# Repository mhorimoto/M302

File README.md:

M302 Arduino UECS SIMPLE NODE Shield 汎用簡易観測ノード
======================================================

# 概要

Arduino UNOのシールドとして UECS で農業環境計測で使用しやすい
センサ類の接続に特化した基板。

## 初版 (1.00)
  commit 2f4df36819d791f5551f218545c303c0058bd9ba
  * I2CとLANとIM920の接続インタフェースを持ったもの。

## 1.10
  * I2CとLANとADC入力とIM920の接続インタフェースを持ったもの。
  * 製作ワークショップなどで使用する用途も考慮。

## K2版 (改２

KiCAD 7.x 対応.

以下予定。

  * HX711を搭載する
  * SMDを多用する
  * W5500を搭載する
  * 電圧レベルコンバーターを搭載する

# Interface仕様

 I2Cは5V仕様。IM920を接続するためだけにレベルコンバータを使用。

## I2C

 便宜的にシルク面にJ1〜J4は名前を記しているが、いずれもI2Cなので、以下のピン配置で同じく使用できる。なお、必要に応じてセンサ側でプルアップをするように。

 | PIN | 意味 |
 |-----|------|
 |  1  | GND  |
 |  2  | +5V  |
 |  3  | SDA  |
 |  4  | SCL  |

 J5はELT社のCO2センサD-400用のインタフェースである。基本的にI2Cであるが、リセット端子を個別に用意している。

 | PIN | 意味 |
 |-----|------|
 |  1  | +5V  |
 |  2  | N/C  |
 |  3  | GND  |
 |  4  | SDA  |
 |  5  | N/C  |
 |  6  | RST  |
 |  7  | SCL  |

## アナログ入力

Arduino UNOの10bits A/Dコンバータ(以降、ADC)を手軽に使用するために4chのコネクタをJ9(ANALOG-IN)として用意している。

 | PIN | 意味 |
 |-----|------|
 |  1  | Ch1  |
 |  2  | GND  |
 |  3  | Ch2  |
 |  4  | GND  |
 |  5  | Ch3  |
 |  6  | GND  |
 |  7  | Ch4  |
 |  8  | GND  |

## IM920接続インタフェース

920MHz伝送用無線通信モジュールIM920を接続するためのシリアルインタフェースを用意している。IM920が3.3V仕様なのでレベルコンバータを実装する。(IM920を使用しない場合にはレベルコンバータは不要)

 | PIN |   意味   |
 |-----|----------|
 |  1  | RESET    |
 |  2  | BUSY     |
 |  3  | GND      |
 |  4  | +3.3V    |
 |  5  | IM920 TX |
 |  6  | IM920 RX |

## LANインタフェース

W5500で一般的に販売されているものが接続出来るように用意している。

 | PIN | 意味  |
 |-----|-------|
 |  1  | +3.3V |
 |  2  | +5V   |
 |  3  | MISO  |
 |  4  | GND   |
 |  5  | MOSI  |
 |  6  | RESET |
 |  7  | SS    |
 |  8  | N/C   |
 |  9  | SCLK  |
 | 10  | N/C   |

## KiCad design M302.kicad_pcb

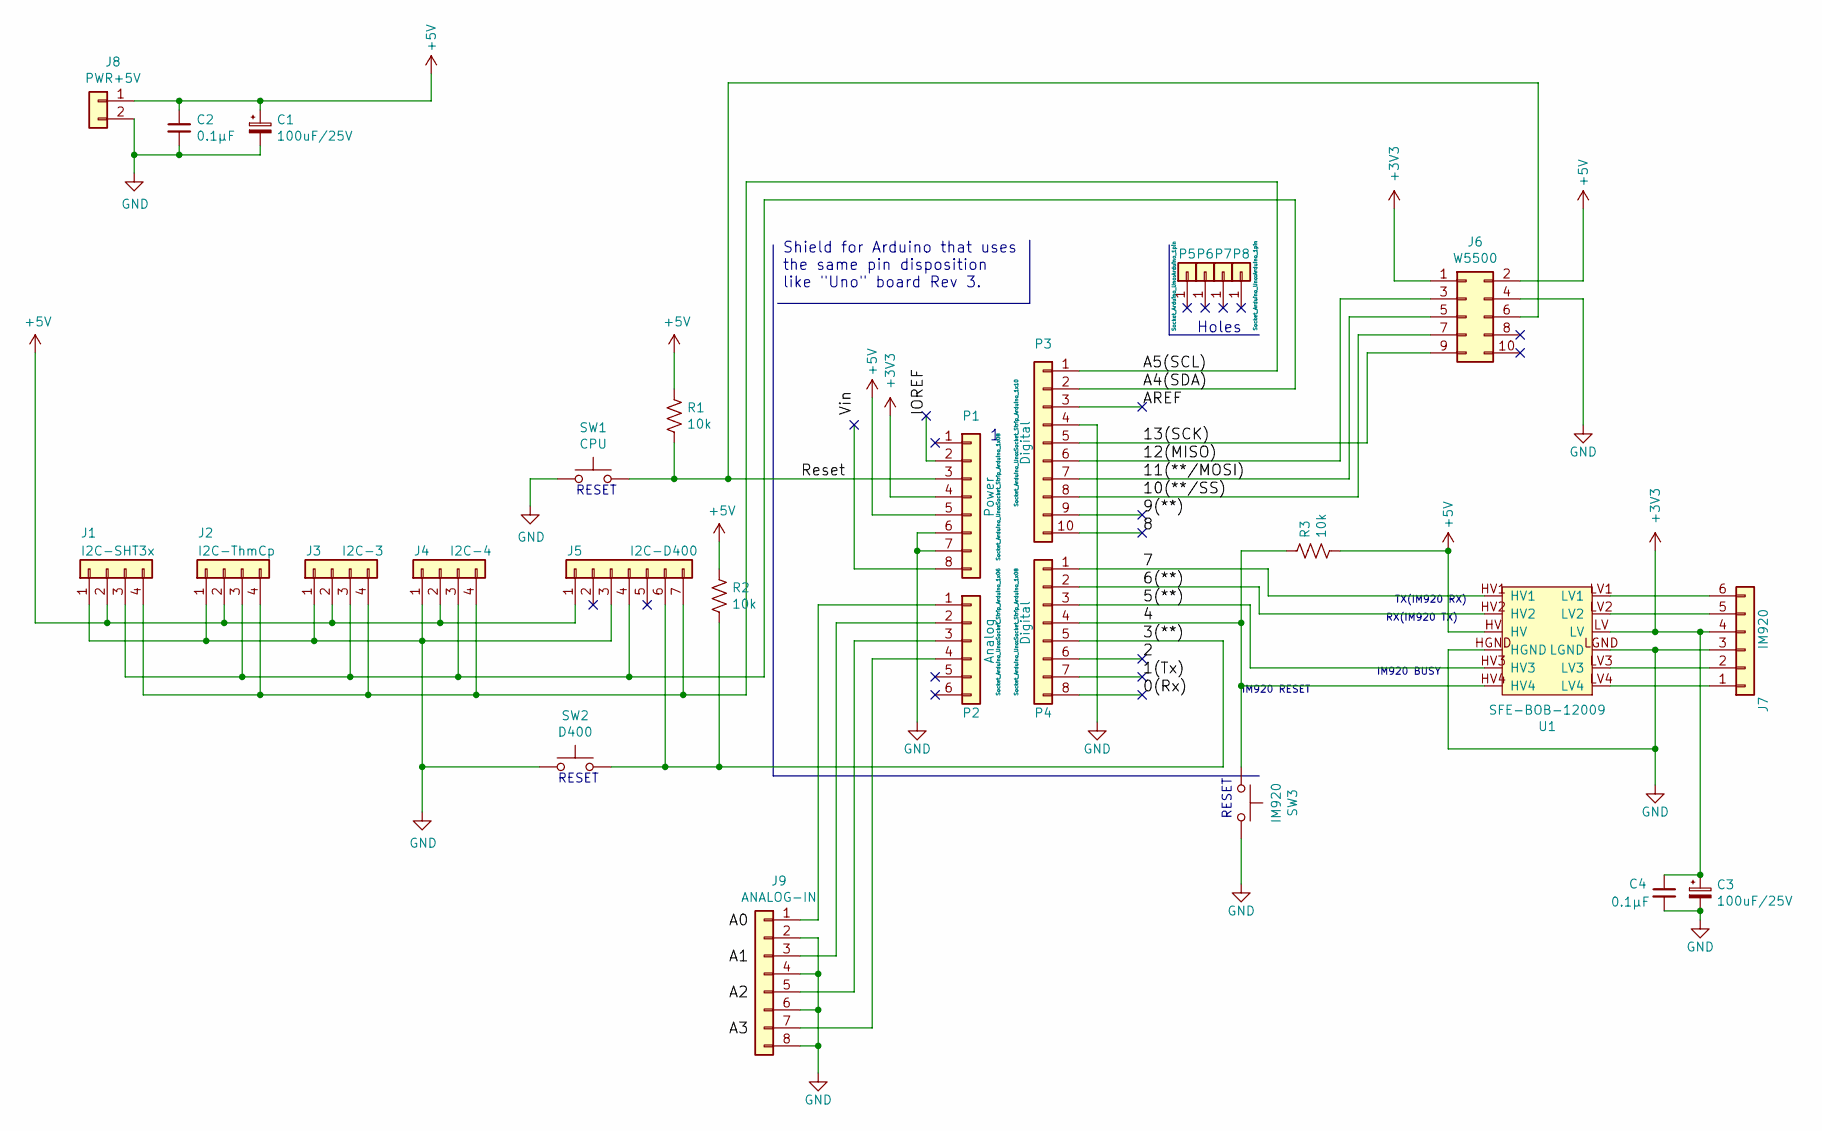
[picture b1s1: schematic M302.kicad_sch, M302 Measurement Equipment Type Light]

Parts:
C1, C3: 100uF/25V; CP_Radial_D5.0mm_P2.00mm
C2, C4: 0.1μF; C_Disc_D3.0mm_W2.0mm_P2.50mm
J1: I2C-SHT3x; JST_XH_B4B-XH-A_1x04_P2.50mm_Vertical
J2: I2C-ThmCp; JST_XH_B4B-XH-A_1x04_P2.50mm_Vertical
J3: I2C-3; JST_XH_B4B-XH-A_1x04_P2.50mm_Vertical
J4: I2C-4; JST_XH_B4B-XH-A_1x04_P2.50mm_Vertical
J5: I2C-D400; JST_XH_B7B-XH-A_1x07_P2.50mm_Vertical
J6: W5500; PinHeader_2x05_P2.54mm_Vertical
J7: IM920; JST_XH_B6B-XH-A_1x06_P2.50mm_Vertical
J8: PWR+5V; JST_XH_B2B-XH-A_1x02_P2.50mm_Vertical
J9: ANALOG-IN; JST_XH_B8B-XH-A_1x08_P2.50mm_Vertical
P1: Power; Socket_Strip_Arduino_1x08
P2: Analog; Socket_Strip_Arduino_1x06
P3: Digital; Socket_Strip_Arduino_1x10
P4: Digital; Socket_Strip_Arduino_1x08
P5, P6, P7, P8: CONN_01X01; Arduino_1pin
R1, R2, R3: 10k; R_Axial_DIN0207_L6.3mm_D2.5mm_P7.62mm_Horizontal
SW1: CPU; TVDT18-050
SW2: D400; TVDT18-050
SW3: IM920; TVDT18-050
U1: SFE-BOB-12009

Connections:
+3V3: C3.1, C4.1, J6.1, J7.4, P1.4, U1.LV
+5V: C1.1, C2.1, J1.2, J2.2, J3.2, J4.2, J5.1, J6.2, J8.1, P1.5, R1.1, R2.1, R3.2, U1.HV
/0(Rx): P4.8
/1(Tx): P4.7
/2: P4.6
/3(**): J5.6, P4.5, R2.2, SW2.2
/4: P4.4, R3.1, SW3.1, U1.HV4
/5(**): P4.3, U1.HV3
/6(**): P4.2, U1.HV2
/7: P4.1, U1.HV1
/8: P3.10
/9(**): P3.9
/10(**/SS): J6.7, P3.8
/11(**/MOSI): J6.5, P3.7
/12(MISO): J6.3, P3.6
/13(SCK): J6.9, P3.5
/A4(SDA): J1.3, J2.3, J3.3, J4.3, J5.4, P3.2
/A5(SCL): J1.4, J2.4, J3.4, J4.4, J5.7, P3.1
/AREF: P3.3
/IOREF: P1.2
/Reset: J6.6, P1.3, R1.2, SW1.2
GND: C1.2, C2.2, C3.2, C4.2, J1.1, J2.1, J3.1, J4.1, J5.3, J6.4, J7.3, J8.2, J9.2, J9.4, J9.6, J9.8, P1.6, P1.7, P3.4, SW1.1, SW2.1, SW3.2, U1.HGND, U1.LGND
unnamed: J7.1, U1.LV4
unnamed: J7.2, U1.LV3
unnamed: J7.5, U1.LV2
unnamed: J7.6, U1.LV1
unnamed: J9.1, P2.1
unnamed: J9.3, P2.2
unnamed: J9.5, P2.3
unnamed: J9.7, P2.4

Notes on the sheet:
RESET
RX(IM920 TX)
Shield for Arduino that uses the same pin disposition like "Uno" board Rev 3.
Holes
IM920 BUSY
TX(IM920 RX)
IM920 RESET

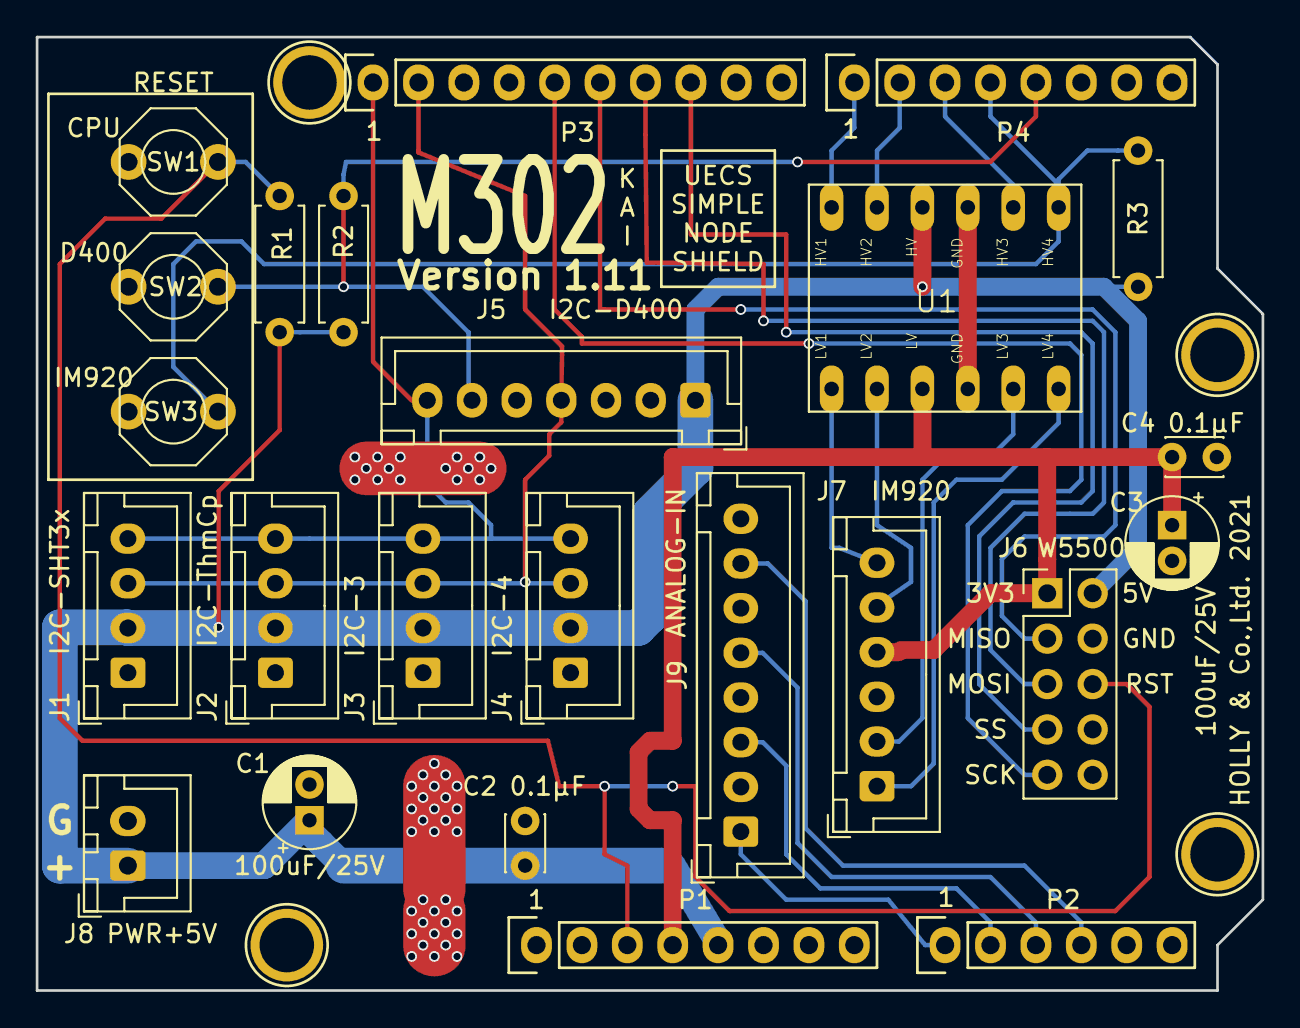
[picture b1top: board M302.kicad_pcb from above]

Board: 2 copper layers, 68.6 x 53.3 mm, 28 parts (0 on the bottom side), 23 nets.

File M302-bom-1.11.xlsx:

品名 Name | 部品番号 Designator | 個数 Quanity | 値 Value | パッケージ Package | 説明 Description | 部品メーカ Manufacturer | メーカ品番 Manufacturer Part Number | 代替可否
抵抗 | R1 R2 R3 | 3 | 10kΩ |  |  | SHIH HAO Electronics | RD16S 10K | Available
コンデンサ | C1 C3 | 2 | 100uF/25V |  |  | Rubycon | 25PK100MEFC5X11 | Available
コンデンサ | C2 C4 | 2 | 0.1uF |  |  | muRata | RPEF11H104Z2P1A01B | Available
XHコネクタ | J1 J2 J3 J4 | 4 | ベース付ポスト・トップ型4P |  | I2C I/F用 | JST | B4B-XH-A(LF)(SN) | Available
XHコネクタ | J5 | 1 | ベース付ポスト・トップ型7P |  | D400 I/F用 | JST | B7B-XH-A(LF)(SN) | Available
Pin Header | J6 | 1 | 2.54mmピッチピンヘッダ 2x5 |  | W5500 I/F用 | Useconn Electronics | PH2X5SG | Available
XHコネクタ | J7 | 1 | ベース付ポスト・トップ型6P |  | IM920 I/F用 | JST | B6B-XH-A(LF)(SN) | Available
XHコネクタ | J7 | 1 | ベース付ポスト・トップ型2P |  | POWER用 | JST | B2B-XH-A(LF)(SN) | Available
XHコネクタ | J9 | 1 | ベース付ポスト・トップ型8P |  | ADC用 | JST | B8B-XH-A(LF)(SN) | Available
Arduino Pin Header | P1 P4 | 2 | ピンソケット 1x8 リード長 10mm |  | Arduino Long Pin | Useconn Electronics | FH105-1x8SG/RH | Available
Arduino Pin Header | P2 | 1 | ピンソケット 1x6 リード長 10mm |  | Arduino Long Pin | Useconn Electronics | FH105-1x6SG/RH | Available
Arduino Pin Header | P3 | 1 | ピンソケット 1x10 リード長 10mm |  | Arduino Long Pin | Useconn Electronics | FH105-1x10SG/RH | Available
タクトスイッチ | SW1 | 1 | タクトスイッチ・1回路1接点・赤 |  | CPU RESET | Zhejiang Jianfu Electronics | TVDT18-050CR-T | Available
タクトスイッチ | SW2 SW3 | 2 | タクトスイッチ・1回路1接点・白 |  | I/O RESET | Zhejiang Jianfu Electronics | TVDT18-050CW-T | Available

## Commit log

2020-10-03 とりあえず
2020-10-03 VSWは不要なので外す
2020-10-04 現在基板確認中
2021-01-06 1st release
2021-01-13 printout:
2021-01-14 sch: 1.10 PullUp抵抗とアナログインプットを増やす
2021-01-15 M302改 v1.10 PCB作業途中
2021-01-15 pcb: M302改 v1.10 PCB作業一旦終了
2021-01-15 pcb: v1.10 3D画像作成。もう少しシルクとドキュメントを追加予定
2021-02-24 sche: board: docs:
2021-02-24 rel: 1.10
2021-02-24 rel: 1.11 コンデンサ3Dモデル変更
2021-02-24 sche: Rev変更1.11へ
2021-02-26 docs: 回路図PDF出力
2021-03-10 1.11 PCBgogo向けにBOM関連資料準備
2021-04-24 feat: テストプログラム追加
2021-04-26 docs: 動画制作
2021-04-30 test: W5500テストプログラム追加
2021-06-20 TK01: トレーニングキット用プログラム作成開始
2021-06-21 feat: lowcore初期化完成
2021-06-21 必要ファイルのコピーまで終了
2021-07-05 feat: 一応センサ無しでloop動作まで完了
2021-07-20 feat:EEPROMのデータ配置を変更する。MACアドレスの最下位を+30してROOMに割り付ける。
2021-07-23 feat: HTTPを追加。GETで実験まで
2021-07-25 feat: V040 だいたい出来た。なぜか110分でrebootする。
2021-07-28 feat,docs: V042リリース初版。ドキュメントはこれから。
2021-07-29 docs: Releases日を修正。
2021-12-18 M302J PCB途中. Ethernet Moduleのpin配置不明
2022-07-04 KiCAD new version
2022-07-05 backup directory ignore
2022-07-05 docs:ソフトウェアの説明を追加
2022-11-01 回路図のPDF出力の追加
2022-11-01 docs: add BOM
2023-04-22 sche: KiCAD 7.0対応
2023-05-03 docs: K2予定を記述
2023-06-25 cad:
2023-07-07 only open
2024-05-15 KiCAD 8
2024-05-15 KiCAD 8.0
2025-01-28 Lab Support九州 ヴァージョン
2025-02-02 なにか変更
2025-02-05 BOM reset
